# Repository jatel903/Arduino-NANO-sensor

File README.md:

# Arduino NANO sensor board
## v1.0
###### jatel.sk

**Specification:**  
Power supply: 12V DC / 50mA  
Inputs: 2x analog with 1M pull-up resistor  
Output: 1x SPDT contact 0.5A / 125VAC  
Cover: [KM-18B](https://www.tme.eu/sk/details/km-18b/skatulky-pre-poplasne-zariad-a-senzory/maszczyk/km-18b-bk/)  
Programmer: [CH340 Serial Port Debugger USB to TTL Converter](https://www.aliexpress.com/item/32645188490.html?spm=a2g0o.productlist.0.0.66445f43KrMtc2&algo_pvid=d437ea6a-45e1-45a2-b66c-f30d704bff8e&algo_expid=d437ea6a-45e1-45a2-b66c-f30d704bff8e-24&btsid=2100bdd816126106735653811e7d0a&ws_ab_test=searchweb0_0,searchweb201602_,searchweb201603_)  

**Description:**  
The electronic module was originally designed as  a staircase lighting switch. The module transforms the analog output from the [FSR](https://www.conrad.sk/senzor-tlaku-fsr-408.k503372) type pressure sensors into a two-state output with using of a relay.   

The output is a relay potential-free changeover contact 0.5A / 125VAC. The module is compatible with the Arduino nano 328 module, but does not include a USB converter. Therefore, it is necessary to use a standard Arduino USB [converter](https://www.aliexpress.com/item/32645188490.html?spm=a2g0o.productlist.0.0.66445f43KrMtc2&algo_pvid=d437ea6a-45e1-45a2-b66c-f30d704bff8e&algo_expid=d437ea6a-45e1-45a2-b66c-f30d704bff8e-24&btsid=2100bdd816126106735653811e7d0a&ws_ab_test=searchweb0_0,searchweb201602_,searchweb201603_). The module contains a 3-pole DIP switch that can be used to set various program modes. The firmware for FSR sensor does not exist, but the firmware for the [automatic switch of pump for disinfectant liquid](https://github.com/jatel903/pwp12.git)  exists.

**The examples of other possibilities of use:**

* thermostat
* automatic lighting with PIR sensor
* alarm with PIR sensor or radar
* twilight switch
* logger
* automatic watering system
* fluid flow measurement and automatic switching according to the volume of fluid
* automatic switch of a pump for disinfectant liquid, etc  

**All mentioned applications above depend on the firmware, which you have to create yourself.**

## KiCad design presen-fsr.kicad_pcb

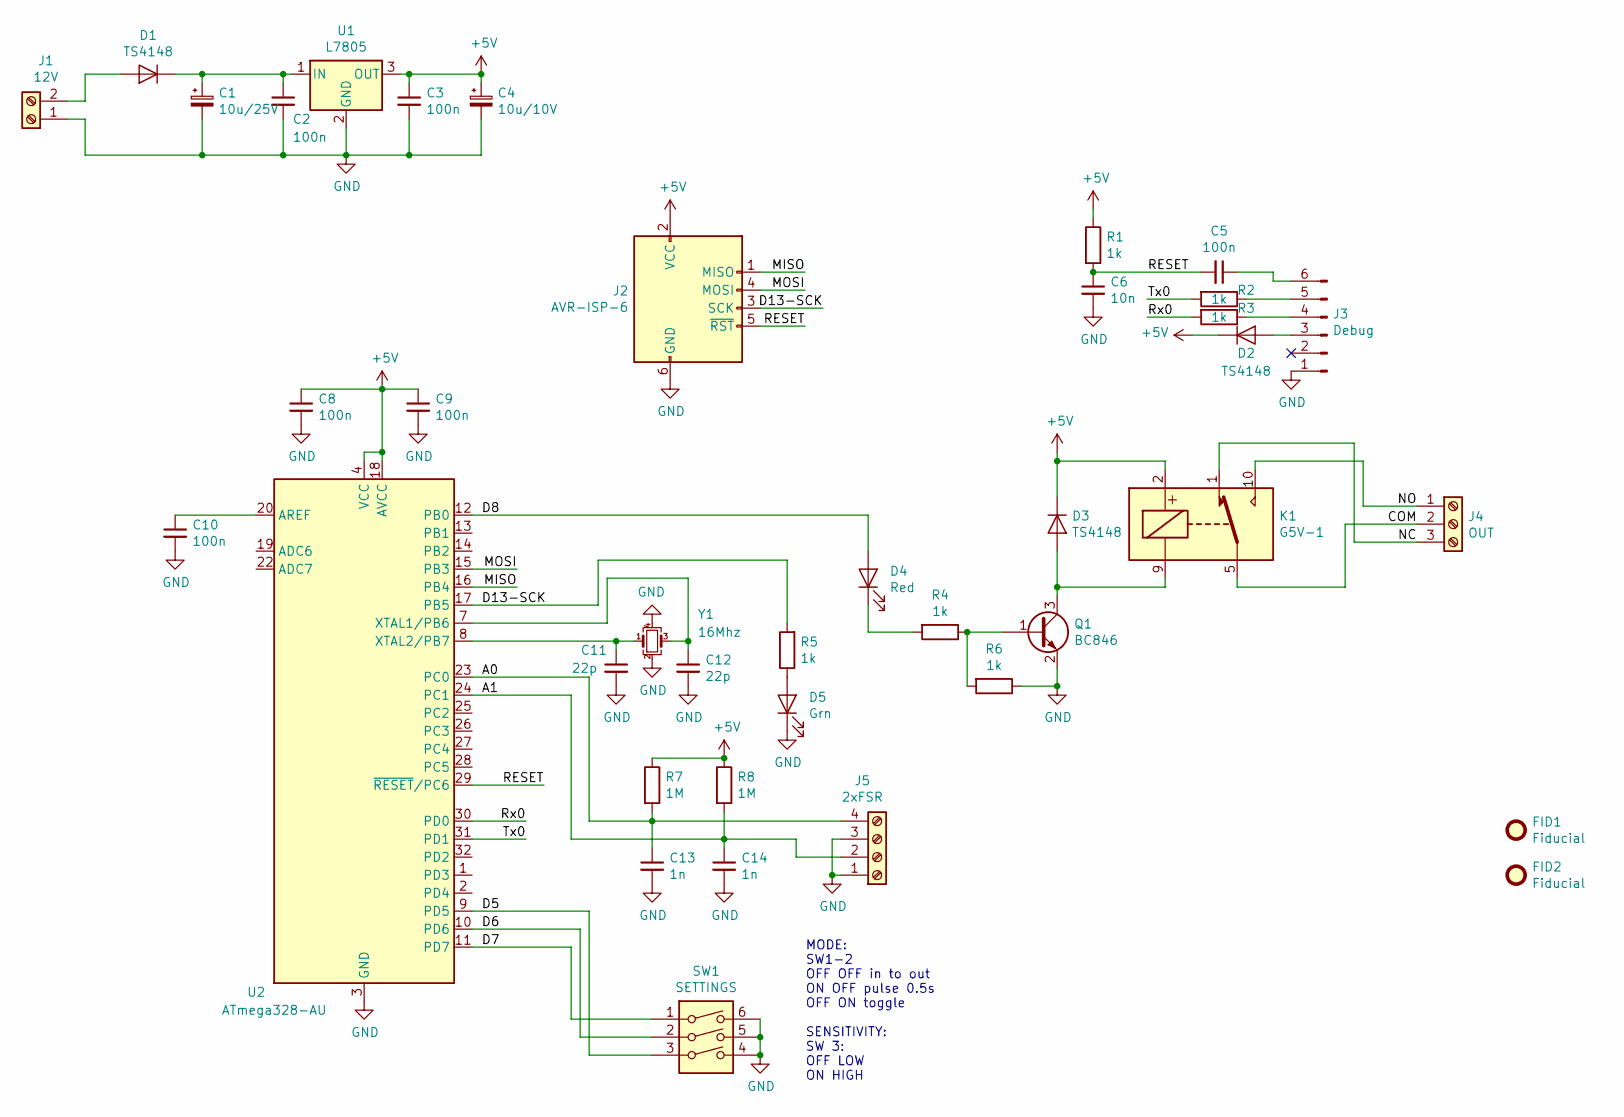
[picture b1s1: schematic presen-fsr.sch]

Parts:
C1: 10u/25V; CP_EIA-6032-20_AVX-F_Pad2.25x2.35mm_HandSolder
C2, C3, C5, C8, C9, C10: 100n; C_0805_2012Metric_Pad1.15x1.40mm_HandSolder
C4: 10u/10V; CP_EIA-3216-12_Kemet-S_Pad1.58x1.35mm_HandSolder
C6: 10n; C_0805_2012Metric_Pad1.15x1.40mm_HandSolder
C11, C12: 22p; C_0805_2012Metric_Pad1.15x1.40mm_HandSolder
C13, C14: 1n; C_0805_2012Metric_Pad1.15x1.40mm_HandSolder
D1, D2, D3: TS4148; D_0805_2012Metric
D4: Red; LED_0805_2012Metric_Pad1.15x1.40mm_HandSolder
D5: Grn; LED_0805_2012Metric_Pad1.15x1.40mm_HandSolder
FID1, FID2: Fiducial; Fiducial_1mm_Mask2mm
J1: 12V; TerminalBlock_Phoenix_MKDS-1,5-2-5.08_1x02_P5.08mm_Horizont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
J2: AVR-ISP-6; PinHeader_2x03_P2.54mm_Vertical
J3: Debug; PinHeader_1x06_P2.54mm_Vertical
J4: OUT; TerminalBlock_Phoenix_MKDS-1,5-3-5.08_1x03_P5.08mm_Horizont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
J5: 2xFSR; TerminalBlock_Phoenix_MKDS-1,5-4-5.08_1x04_P5.08mm_Horizont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
K1: G5V-1; Relay_SPDT_Omron_G5V-1
Q1: BC846; SOT-23
R1, R2, R3, R4, R5, R6: 1k; R_0805_2012Metric_Pad1.15x1.40mm_HandSolder
R7, R8: 1M; R_0805_2012Metric_Pad1.15x1.40mm_HandSolder
SW1: SETTINGS; SW_DIP_SPSTx03_Slide_6.7x9.18mm_W8.61mm_P2.54mm_LowProfile
U1: L7805; TO-252-2
U2: ATmega328-AU; TQFP-32_7x7mm_P0.8mm
Y1: 16Mhz; Crystal_SMD_3225-4Pin_3.2x2.5mm

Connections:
+5V: C3.1, C4.1, C8.1, C9.1, D2.1 (K), D3.1 (K), J2.2 (VCC), K1.2, R1.1, R7.1, R8.1, U1.3 (OUT), U2.4 (VCC), U2.6 (VCC), U2.18 (AVCC)
/A0: C13.1, J5.4, R7.2, U2.23 (PC0)
/A1: C14.1, J5.2, R8.2, U2.24 (PC1)
/COM: J4.2, K1.5, K1.6
/D5: SW1.3, U2.9 (PD5)
/D6: SW1.2, U2.10 (PD6)
/D7: SW1.1, U2.11 (PD7)
/D8: D4.2 (A), U2.12 (PB0)
/D13-SCK: J2.3 (SCK), R5.2, U2.17 (PB5)
/MISO: J2.1 (MISO), U2.16 (PB4)
/MOSI: J2.4 (MOSI), U2.15 (PB3)
/NC: J4.3, K1.1
/NO: J4.1, K1.10
/RESET: C5.2, C6.1, J2.5 (~RST), R1.2, U2.29 (~RESET~/PC6)
/Rx0: R3.2, U2.30 (PD0)
/Tx0: R2.2, U2.31 (PD1)
GND: C1.2, C2.2, C3.2, C4.2, C6.2, C8.2, C9.2, C10.2, C11.2, C12.2, C13.2, C14.2, D5.1 (K), J1.1, J2.6 (GND), J3.1, J5.1, J5.3, Q1.2 (E), R6.1, SW1.4, SW1.5, SW1.6, U1.2 (GND), U2.3 (GND), U2.5 (GND), U2.21 (GND), Y1.2, Y1.4
unnamed: C1.1, C2.1, D1.1 (K), U1.1 (IN)
unnamed: C5.1, J3.6
unnamed: C10.1, U2.20 (AREF)
unnamed: C11.1, U2.8 (XTAL2/PB7), Y1.1
unnamed: C12.1, U2.7 (XTAL1/PB6), Y1.3
unnamed: D1.2 (A), J1.2
unnamed: D2.2 (A), J3.3
unnamed: D3.2 (A), K1.9, Q1.3 (C)
unnamed: D4.1 (K), R4.2
unnamed: D5.2 (A), R5.1
unnamed: J3.4, R3.1
unnamed: J3.5, R2.1
unnamed: Q1.1 (B), R4.1, R6.2

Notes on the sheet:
MODE: SW1-2 OFF OFF in to out ON OFF pulse 0.5s OFF ON toggle SENSITIVITY: SW 3: OFF LOW ON HIGH

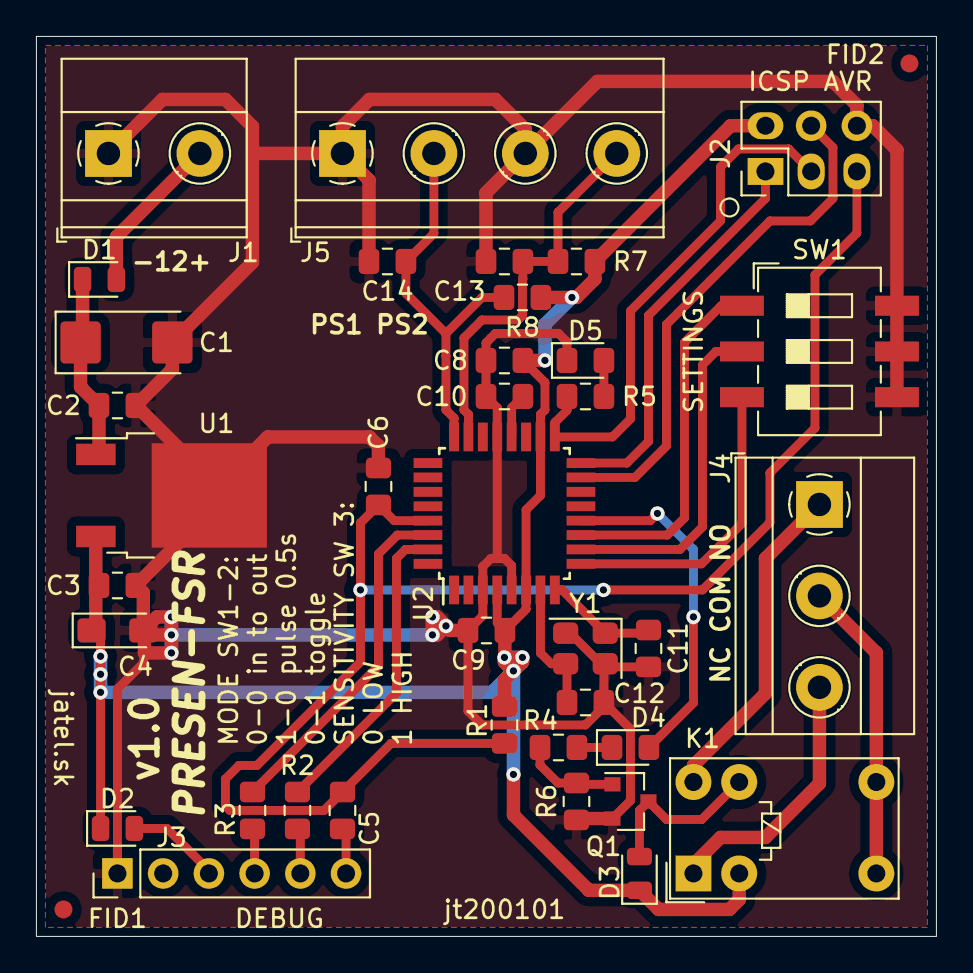
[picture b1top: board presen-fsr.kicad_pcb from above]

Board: 2 copper layers, 50.0 x 50.0 mm, 39 parts (0 on the bottom side), 30 nets.

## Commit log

2020-01-03 Add README.md
2021-01-22 vyroba
2021-01-22 vyroba v cine
2021-02-06 schema pdf
2021-02-06 licencia
2021-02-06 image
2021-02-13 gerber
2021-02-18 otocenie jpg
2021-02-18 .gitignore
2021-02-18 readme EN
2021-02-18 readme
